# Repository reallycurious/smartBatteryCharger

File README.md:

# smartBatteryCharger (incomplete)
PIC12F1572 based Charger for 14.4V cordless drill

<b>Warning:</b> This charger design and accompanying code is based on a lot of assumptions. Some of which may or might not hold true. So if you want to adopt this design and/or code do so at your own risk.

After building a 2 meter by 2 meter cupboard and fastening all screws by hand I decided that a cordless drill is needed. So I bought the most inexpensive one I found. This cordless drill came with a 18v 400ma rated power adapter and charger stand that consists of few simple passive components: A 2W 10 Ohm resistor, an 4007 diode, two 3mm leds and two smd 0805 resistors one 2 KOhm the other 100 Ohm. Oh and instructions to charge 3-5 hours: which resulted in a very hot battery. I feared that it might vent electrolyte so I decided to replace electronics in charger stand, making it smarter.
  
So where to start designing a smart charger circuit that fits in housing of the old dumb one: a net search gave some ideas. Article <a href="https://batteryuniversity.com/learn/article/charging_nickel_based_batteries">Charging Nickel-cadmium @ batteryuniversity.com</a> is helpful but insufficient for designing a charger. <a href="http://electronics-diy.com/electronic_schematic.php?id=813">Intelligent NiCd/NiMH Battery Charger @ electronics-diy.com</a> was better: Although there is no source code as the author states "The source code is not freeware or shareware so please don't ask me to mail you the source code as it has commercial applications" reading the article gives a clear idea on how a smart chager should work and helped me designing the algorithm. <a href="https://electrosome.com/uart-pic-microcontroller-mplab-xc8/">Using UART of PIC Microcontroller – MPLAB XC8 @ electrosome.com</a> was helpful designing uart code. I had no such luck in pwm code, no practical examples for pic12f1572, so I cooked something from datasheet. Thankfully datasheet had sample assembly code for ADC.
  
You might ask, why pic12f1572 ? because with a 3,5 TL price tag for <a href="https://www.direnc.net/pic12f1572t-i-mf-dfn8-8bit-32mhz-mikrodenetleyici">dfn footprint version</a>, it was the cheapest but capable microcontroller that I could find at the time. And except its 10 bit ADC (not 12 bit) I think it is very suitable for the task. I should add that I had not programmed a PIC micro before. I had to learn pic programming (mostly reading the datasheet) for programming the pic12f1572.

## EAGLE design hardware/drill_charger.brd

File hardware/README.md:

<b>WARNING: EXPERIMENTAL DESIGN</b><p>
<b>WARNING: DONT USE LINEAR VOLTAGE REGULATOR</b><p>

Linear Voltage Regulator Heat Up, may fry microcontroller (already had fried one microcontroller with LM7805) 
Currently using <a href="http://www.romanblack.com/smps/smps.htm">http://www.romanblack.com/smps/smps.htm</a> as smps. 
I might also use a buck converter ic.

pcb</img>
<p>
schematic</img>

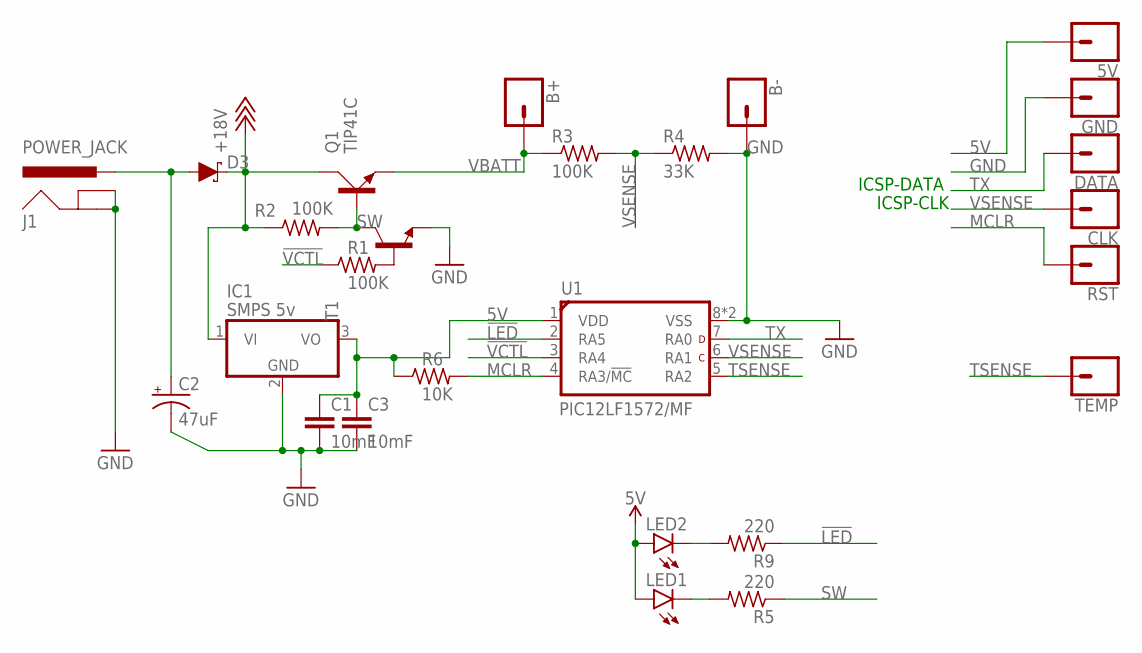
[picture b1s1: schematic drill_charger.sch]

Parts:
5V: CONN_01; 1X01
B+: CONN_01; 1X01
B-: CONN_01; 1X01
C1, C3: 10mF; C0805
C2: 47uF; CPOL-RADIAL-2.5MM-6.5MM
CLK: CONN_01; 1X01
D3: 1A/40V/500mV; SMA-DIODE
DATA: CONN_01; 1X01
GND: CONN_01; 1X01
IC1: SMPS 5v; TO220V
J1: POWER_JACK; POWER_JACK_PTH
LED1, LED2: LED3MM
Q1: TIP41C; TO220AV
R1, R2: 100K; R0805
R3: 100K; R1206
R4: 33K; R1206
R5, R9: 220; R0805
R6: 10K; R0805
RST: CONN_01; 1X01
T1: MMBT3904LT1-NPN-SOT23-BEC; SOT23-BEC
TEMP: CONN_01; 1X01
U1: PIC12LF1572/MF; DFN8-MF

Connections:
5V: 5V.1, C1.1, C3.1, IC1.3 (VO), LED1.A, LED2.A, R6.1, U1.1 (VDD)
!LED: R9.1, U1.2 (RA5)
!VCTL: R1.1, U1.3 (RA4)
+18V: D3.C, IC1.1 (VI), Q1.C, R2.1
GND: B-.1, C1.2, C2.2 (-), C3.2, GND.1, IC1.2 (GND), J1.GND, J1.GNDBREAK, R4.2, T1.E, U1.8 (VSS), U1.EP (VSS)
MCLR: R6.2, RST.1, U1.4 (RA3/!MC!)
unnamed: LED2.K (C), R9.2
unnamed: LED1.K (C), R5.2
unnamed: C2.1 (+), D3.A, J1.PWR
unnamed: R1.2, T1.B
SW: Q1.B, R2.2, R5.1, T1.C
TSENSE: TEMP.1, U1.5 (RA2)
TX: DATA.1, U1.7 (RA0)
VBATT: B+.1, Q1.E, R3.1
VSENSE: CLK.1, R3.2, R4.1, U1.6 (RA1)

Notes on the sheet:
ICSP-DATA
ICSP-CLK

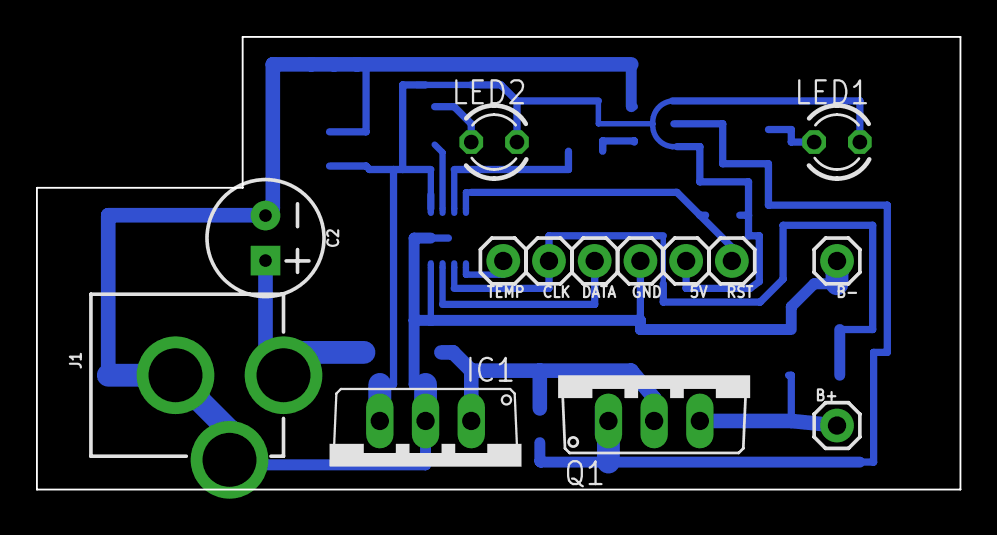
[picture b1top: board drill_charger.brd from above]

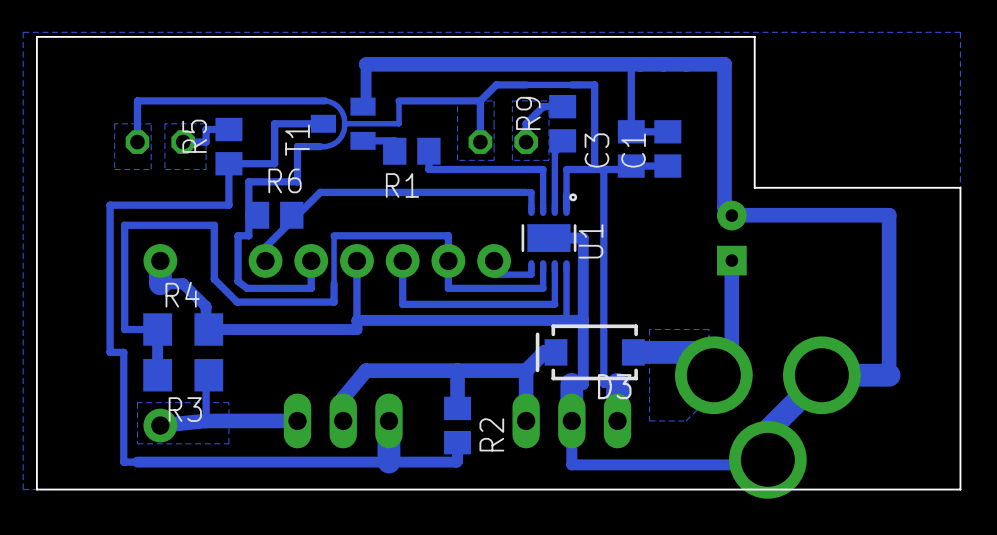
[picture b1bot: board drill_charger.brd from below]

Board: 2 copper layers, 51.3 x 25.1 mm, 26 parts (12 on the bottom side), 15 nets.

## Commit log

2019-07-23 Somewhat working code
2019-07-23 somewhat working code and hardware
2019-07-24 pwm code & cleanup
2019-07-24 code cleanup
2019-07-24 cleanup
2019-12-25 Update README.md
    add incomplete

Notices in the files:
parts and their libraries:
SparkFun-Connectors: Licensing: Creative Commons ShareAlike 4.0 International - https://creativecommons.org/licenses/by-sa/4.0
